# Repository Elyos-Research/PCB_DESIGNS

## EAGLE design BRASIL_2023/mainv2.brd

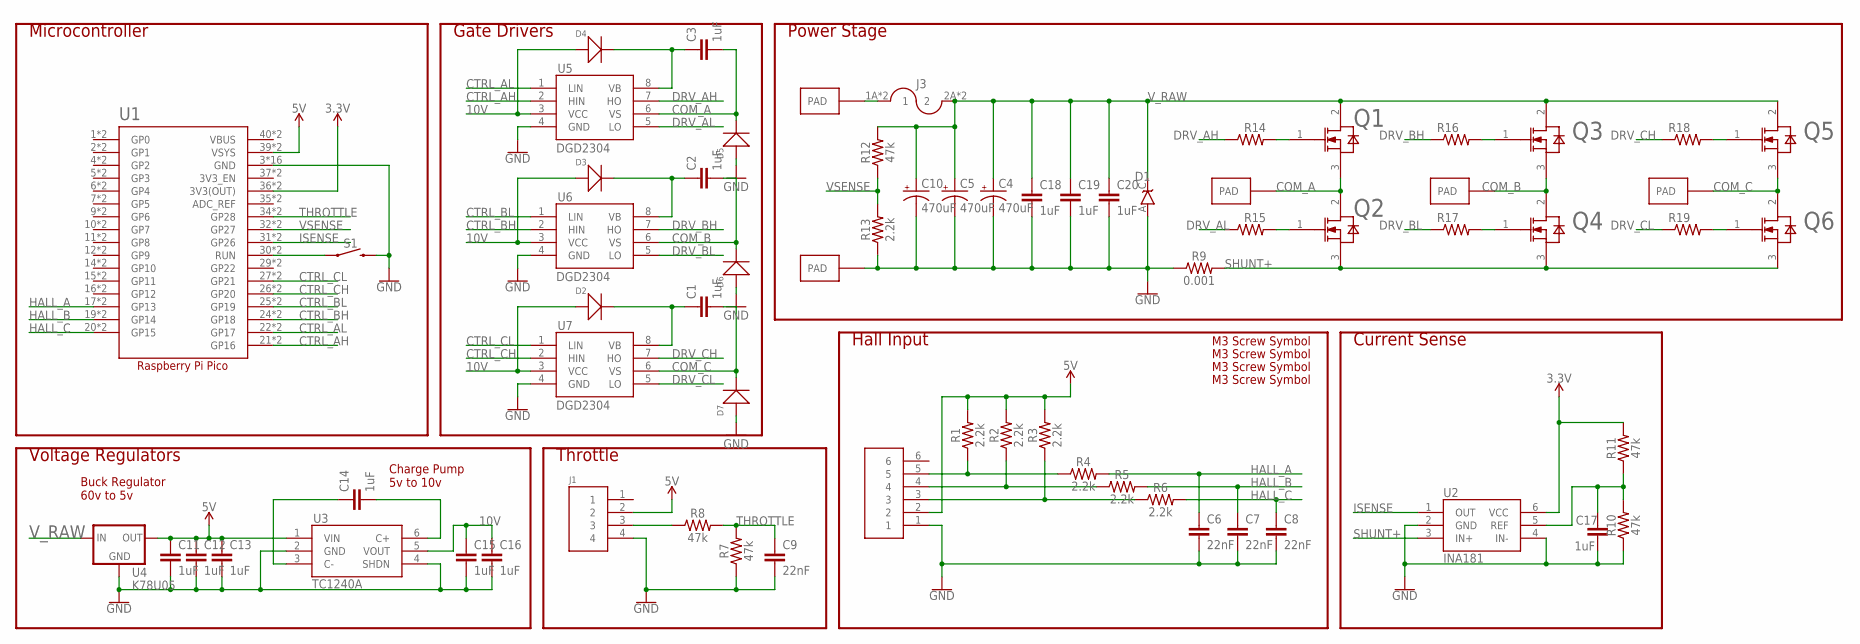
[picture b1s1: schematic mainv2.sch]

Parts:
C1, C2, C3, C11, C12, C13, C14, C15, C16, C17, C18, C19, C20: 1uF; 1206
C4, C5, C10: 470uF; CPOL-RADIAL-5MM-10MM
C6, C7, C8, C9: 22nF; 1206
D1: TVS; DO-214AC
D2, D3, D4, D5, D6, D7: SMD-DIODE-100V-200MA(SOD-123); SOD-123
J1: HEADER4VALULOK; 4PINVALULOK
J2: HEADER6; 6PINVALULOK
J3: FUSE; AUTO_FUSE
Q1, Q2, Q3, Q4, Q5, Q6: IRF135S203; TO254P1524X508-4_3N
R1, R2, R3, R4, R5, R6, R13: 2.2k; 1206
R7, R8, R10, R11, R12: 47k; 1206
R9: 0.001; R2512
R14, R15, R16, R17, R18, R19: R-US_R1206; R1206
S1: MOMENTARY-SWITCH-SPST-PTH-6.0MM; TACTILE_SWITCH_PTH_6.0MM
U1: RASPBERRY_PICO-NO_DEBUG; PICO-PKG-NO_DEBUG
U2: INA181; SOT23-6
U3: TC1240A; SOT23-6
U4: K78U05; V78W_BACKWARDS
U5, U6, U7: DGD2304; SOIC8
U$4, U$5, U$6, U$7, U$8: PAD
U$10, U$11, U$12, U$13: SCREW; M3HOLE

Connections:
3.3V: R11.2, U1.36 (3V3(OUT)), U1.P$36 (3V3(OUT)), U2.6 (VCC)
5V: C11.1, C12.1, C13.1, J1.2, J2.2, R1.2, R2.2, R3.2, U1.39 (VSYS), U1.P$39 (VSYS), U3.1 (VIN), U4.OUT
10V: C15.1, C16.1, D2.+, D3.+, D4.+, U3.5 (VOUT), U5.3 (VCC), U6.3 (VCC), U7.3 (VCC)
COM_A: C3.2, D5.-, Q1.3 (SOURCE), Q2.2 (DRAIN), U5.6 (VS), U$6.PAD
COM_B: C2.2, D6.-, Q3.3 (SOURCE), Q4.2 (DRAIN), U6.6 (VS), U$7.PAD
COM_C: C1.2, D7.-, Q5.3 (SOURCE), Q6.2 (DRAIN), U7.6 (VS), U$8.PAD
CTRL_AH: U1.21 (GP16), U1.P$21 (GP16), U5.2 (HIN)
CTRL_AL: U1.22 (GP17), U1.P$22 (GP17), U5.1 (LIN)
CTRL_BH: U1.24 (GP18), U1.P$24 (GP18), U6.2 (HIN)
CTRL_BL: U1.25 (GP19), U1.P$25 (GP19), U6.1 (LIN)
CTRL_CH: U1.26 (GP20), U1.P$26 (GP20), U7.2 (HIN)
CTRL_CL: U1.27 (GP21), U1.P$27 (GP21), U7.1 (LIN)
DRV_AH: R14.1, U5.7 (HO)
DRV_AL: R15.1, U5.5 (LO)
DRV_BH: R16.1, U6.7 (HO)
DRV_BL: R17.1, U6.5 (LO)
DRV_CH: R18.1, U7.7 (HO)
DRV_CL: R19.1, U7.5 (LO)
GND: C4.-, C5.-, C6.2, C7.2, C8.2, C9.2, C10.-, C11.2, C12.2, C13.2, C15.2, C16.2, C17.2, C18.2, C19.2, C20.2, D1.A, D5.+, D6.+, D7.+, J1.4, J2.1, R7.1, R9.1, R10.1, R13.1, S1.3 (2), U1.3 (GND), U1.8 (GND), U1.13 (GND), U1.18 (GND), U1.23 (GND), U1.28 (GND), U1.33 (GND), U1.38 (GND), U1.P$3 (GND), U1.P$8 (GND), U1.P$13 (GND), U1.P$18 (GND), U1.P$23 (GND), U1.P$28 (GND), U1.P$33 (GND), U1.P$38 (GND), U2.2 (GND), U2.4 (IN-), U3.2 (GND), U3.4 (SHDN), U4.GND, U5.4 (GND), U6.4 (GND), U7.4 (GND), U$5.PAD
HALL_A: C6.1, R4.2, U1.17 (GP13), U1.P$17 (GP13)
HALL_B: C7.1, R5.2, U1.19 (GP14), U1.P$19 (GP14)
HALL_C: C8.1, R6.2, U1.20 (GP15), U1.P$20 (GP15)
ISENSE: U1.31 (GP26), U1.P$31 (GP26), U2.1 (OUT)
unnamed: C2.1, D3.-, U6.8 (VB)
unnamed: J2.3, R3.1, R6.1
unnamed: C3.1, D4.-, U5.8 (VB)
unnamed: J2.4, R2.1, R5.1
unnamed: Q3.1 (GATE), R16.2
unnamed: J2.5, R1.1, R4.1
unnamed: J1.3, R8.1
unnamed: C1.1, D2.-, U7.8 (VB)
unnamed: S1.1, U1.30 (RUN), U1.P$30 (RUN)
unnamed: C17.1, R10.2, R11.1, U2.5 (REF)
unnamed: Q5.1 (GATE), R18.2
unnamed: Q1.1 (GATE), R14.2
unnamed: Q2.1 (GATE), R15.2
unnamed: Q4.1 (GATE), R17.2
unnamed: Q6.1 (GATE), R19.2
unnamed: C14.1, U3.3 (C-)
unnamed: C14.2, U3.6 (C+)
SHUNT+: Q2.3 (SOURCE), Q4.3 (SOURCE), Q6.3 (SOURCE), R9.2, U2.3 (IN+)
THROTTLE: C9.1, R7.2, R8.2, U1.34 (GP28), U1.P$34 (GP28)
VBUS: U1.40 (VBUS), U1.P$40 (VBUS)
VSENSE: R12.1, R13.2, U1.32 (GP27), U1.P$32 (GP27)
V_PREFUSE: J3.1A (1), J3.1B (1), U$4.PAD
V_RAW: C4.+, C5.+, C10.+, C18.1, C19.1, C20.1, D1.C, J3.2A (2), J3.2B (2), Q1.2 (DRAIN), Q3.2 (DRAIN), Q5.2 (DRAIN), R12.2, U4.IN

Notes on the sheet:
Power Stage
Hall Input
Gate Drivers
Throttle
Microcontroller
Voltage Regulators
Current Sense
Buck Regulator 60v to 5v
Charge Pump 5v to 10v

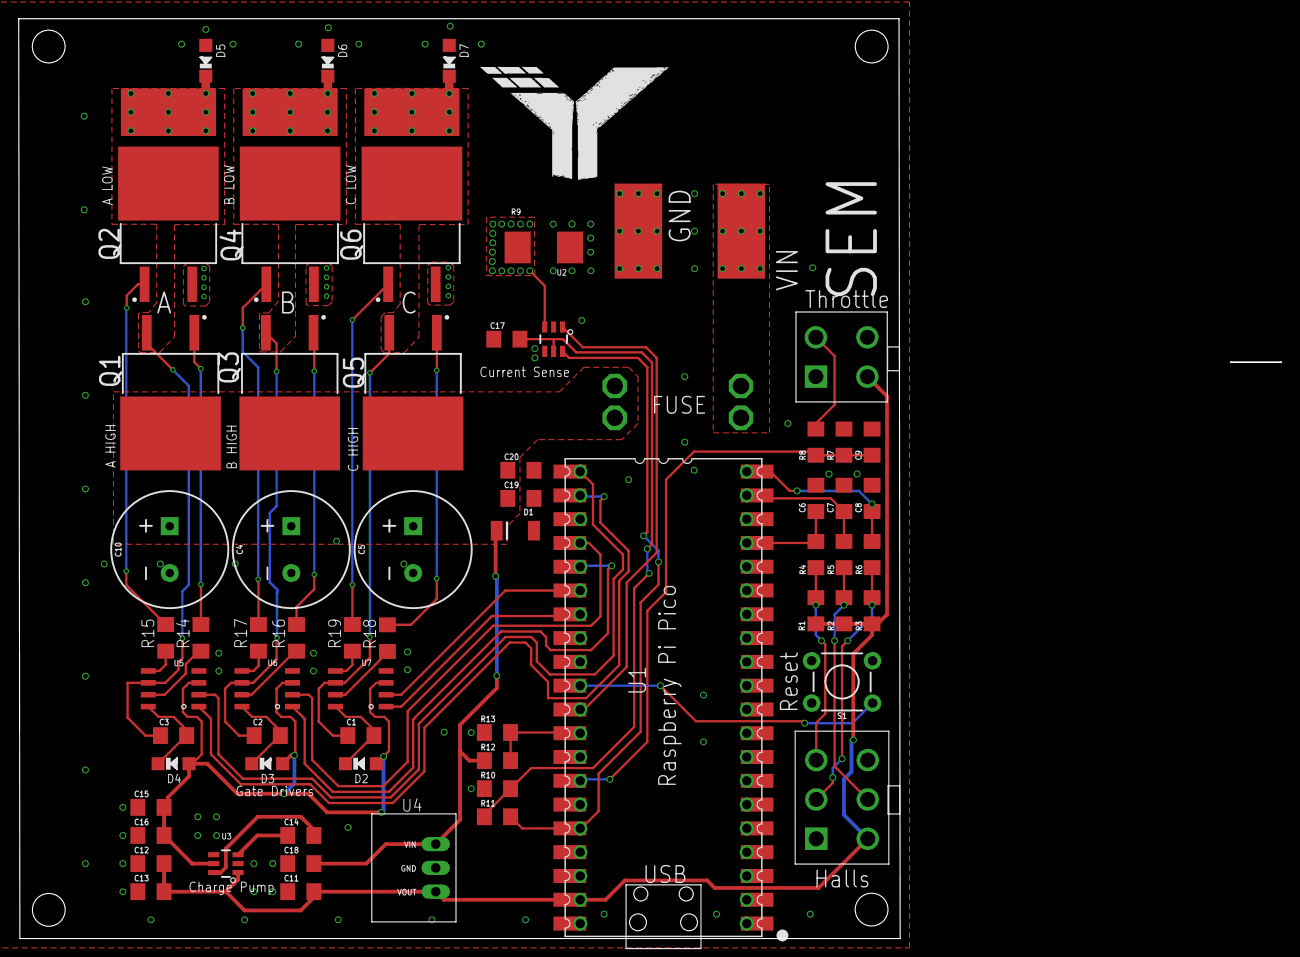
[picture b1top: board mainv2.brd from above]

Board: 2 copper layers, 134.8 x 98.2 mm, 72 parts (0 on the bottom side), 46 nets.

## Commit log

2024-01-31 Version 1.0
2024-01-31 Version 1.0 (2)
2024-02-12 FOC_Design_upload
2024-02-14 Version shunt
2024-03-08 folders
2024-03-09 Create README.m
    folder indy, creado
2024-03-09 Create BRASIL_2023
    folder brasil creado
2024-03-09 Create folder brasil bien
2024-03-09 placa funcional du BRESIL
2024-03-09 placa con diodos, pero con error
2024-03-22 Telemetry PCB China V1
2024-03-22 Inner Motor PCB for hall sampling V1

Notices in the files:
parts and their libraries:
SparkFun-Capacitors: Licensing: Creative Commons ShareAlike 4.0 International - https://creativecommons.org/licenses/by-sa/4.0
